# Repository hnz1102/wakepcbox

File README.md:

<div align="center">
  <h1><code>Wake PC Box</code></h1>
  
</div>

# Wake PC Box - Wake On LAN Packet Transmitting Box

Video

This is the small control box that can wake up the PC using Wake On LAN. You can just push a button, PCs will wake up from the power off status.
There is no need to start up another PC in order to start up a PC with Wake On Lan. Wake on LAN packets are sent via WiFi LAN.
The Box has a battery, and you can charge it from a USB Type-C port. Once charging full, you can use it for a month. If any buttons are not pressed for the specified time (default 30 seconds), the box will sleep automatically and conserve battery power. Up to four PCs can be registered.

# Update History
- 2024-05-30 : Initial Release
- 2026-02-14 : Update code for ESP-IDF V5.4.2 and update README.md
- 2026-06-20 : v0.2.0 - Add WPS PBC mode support, fix WPS display overlap, fix WiFi menu not reflecting WPS credentials immediately

# How it works

This box can send a Wake on LAN packet to the Wireless Access Point. To transfer the packet, the Access Point needs to be set to `Bridge Mode`. If `Router Mode` is set, the Access Point won't transfer to the wired LAN. 

# Feature

**Quick Wake Up** -  Simply press one of the up, down, left, or right buttons to turn on the PC corresponding to that button. 4 PCs can be registered.

**Microcontroller on board** - No need for a PC when you turn on another PC. Directly send packets to the target PCs. 

**Transmit a packet via WiFi** - Wake-on LAN packets are transmitted via Wireless Network.

**Battery Powered** - Using LiPo battery. It can run for a month (In this case, every day a few times used).

**Small Handy Box** - This box is only 60mm(W) x 23mm(H) x 80mm(D) size. No need for any cables, it works. 

**Configurable** - Setting parameters are set from the display menu. SSID/Password/Target PC Hardware Address(4 PCs)/Time Zone/Sleep Time/Sleep Mode/Display Off Time/Reset Settings.

**WPS Support** - If `wps_enable = "true"` and `wifi_ssid` is empty in `cfg.toml`, the device enters WPS PBC (Push Button Configuration) mode on first boot. Press the WPS button on your router within 120 seconds. The obtained SSID and password are saved to NVS automatically, and subsequent boots connect normally without WPS.

# How to Use the Box
At first, you can set the WiFi SSID and PSK-Password in one of two ways:

**Option A: Manual entry via menu** - Push the Center Key to open the setting menu, select `WiFi`, then enter your SSID and password using the direction keys.

**Option B: WPS PBC mode** - Set `wps_enable = "true"` and leave `wifi_ssid` empty in `cfg.toml` before flashing. On first boot, the device displays "WPS MODE" and waits up to 120 seconds. Press the WPS button on your router to transfer the credentials automatically. The SSID and password are saved and WPS mode is disabled for subsequent boots.
Next, set the Hardware Address(Ethernet MAC Address) of the PC that you want to wake up. Select `HW Address` and push Center Key, select from `PC1` to `PC4`, push Center key, then enter your Hardware Address like `00:11:22:33:44:55`. 

After setting, just push button corresponding the target.(Up Key : PC1, Down Key : PC2, Left Key: PC3, Right Key: PC4)

To charge a battery, just connect to a USB Type-C port from the bus-powered USB port. During the charge, the CHG LED is RED ON. After the charging is full, the FUL LED is GREEN ON. And the charging will be stopped automatically.

Assembled PCB

Set in Box

# How to build from code and Install to the unit.

Using Ubuntu 22.04.3 LTS and ESP-IDF V5.4.2

1. Install Rust Compiler
```bash
sudo apt update && sudo apt -y install git python3 python3-pip gcc build-essential curl pkg-config libudev-dev libtinfo5 clang libclang-dev llvm-dev udev libssl-dev python3.10-venv
curl --proto '=https' --tlsv1.2 -sSf https://sh.rustup.rs | sh
```
You can see the install menu, select No.1. After installation, set the environment variable.

```bash
. "$HOME/.cargo/env"
```

2. Install toolchain for ESP32-C3
```bash
cargo install ldproxy
cargo install espup
cargo install cargo-espflash
```

3. Install ESP-IDF and set the environment variable.
```bash
espup install
espup update
```

Then, run the following command to set the environment for the ESP32-C3 toolchain:
```bash
. ./export-esp.sh
```

4. Add UDEV rules
```bash
sudo sh -c 'echo "SUBSYSTEMS==\"usb\", ATTRS{idVendor}==\"303a\", ATTRS{idProduct}==\"1001\", MODE=\"0666\"" > /etc/udev/rules.d/99-esp32.rules'
sudo udevadm control --reload-rules
sudo udevadm trigger
```

5. Download Current-Logger code
```bash
git clone https://github.com/hnz1102/wakepcbox.git
cd wakepcbox
``` 
6. Setting WiFi SSID, Password, and InfluxDB server IP address.
```bash
cfg.toml

[wakepcbox]
wifi_ssid = "<SSID>"      # Set your AP SSID. Leave empty to use WPS mode.
wifi_psk = "<Password>"   # Set password for SSID.
wps_enable = "false"       # Set "true" to use WPS PBC mode on first boot (requires wifi_ssid to be empty).
target_mac_address1 = "00:00:00:00:00:00"  # Set Hardware Address(MAC Address) for wakeup.
target_mac_address2 = "00:00:00:00:00:00"
target_mac_address3 = "00:00:00:00:00:00"
target_mac_address4 = "00:00:00:00:00:00"
timezone_offset = "0"
idle_in_sleep_time = "30"
sleep_mode = "light"
display_off_time = "30"
wakeup_interval = "10"
```
7. Build code and writing flash
```bashbash
cargo build --release
```

8. Connecting the board and Set device and set toolchain.

Connecting the Box by USB Type-C to this code building PC. Then, 

```bash
cargo espflash board-info

✔ Use serial port '/dev/ttyACM0' - USB JTAG/serial debug unit? · yes
✔ Remember this serial port for future use? · yes
[2026-02-14T04:41:35Z INFO ] Serial port: '/dev/ttyACM0'
[2026-02-14T04:41:35Z INFO ] Connecting...
[2026-02-14T04:41:36Z INFO ] Using flash stub
Chip type:         esp32c3 (revision v0.4)
Crystal frequency: 40 MHz
Flash size:        4MB
Features:          WiFi, BLE
MAC address:       a0:76:4e:b3:64:c0

Security Information:
=====================
Flags: 0x00000000 (0)
Key Purposes: [0, 0, 0, 0, 0, 0, 12]
Chip ID: 5
API Version: 3
Secure Boot: Disabled
Flash Encryption: Disabled
SPI Boot Crypt Count (SPI_BOOT_CRYPT_CNT): 0x0
```

9. Writing flash
```bash
cargo espflash flash --release --monitor

[2026-02-14T04:43:53Z INFO ] Serial port: '/dev/ttyACM0'
[2026-02-14T04:43:53Z INFO ] Connecting...
[2026-02-14T04:43:53Z INFO ] Using flash stub
   Compiling wakepcbox v0.1.0 (/wakepcbox)
    Finished `release` profile [optimized] target(s) in 4.22s
Chip type:         esp32c3 (revision v0.4)
Crystal frequency: 40 MHz
Flash size:        4MB
Features:          WiFi, BLE
MAC address:       a0:76:4e:b3:64:c0
App/part. size:    1,644,080/3,145,728 bytes, 52.26%
[00:00:00] [========================================]      13/13      0x0      Verifying... OK!                                                                                                                                                       [00:00:00] [========================================]       1/1       0x8000   Skipped! (checksum matches)                                                                                                                                            
[00:00:15] [========================================]     887/887     0x10000  Verifying... OK!                                                                                                                                                       [2026-02-14T04:44:16Z INFO ] Flashing has completed!

And automatically boot!
```
## Schematic, PCB Gabar and Container 3D Data

There is a Schematic data in the hardware directory including 3D printing data. 

## LICENSE
This source code is licensed under MIT. Other Hardware Schematic documents are licensed under CC-BY-SA V4.0.

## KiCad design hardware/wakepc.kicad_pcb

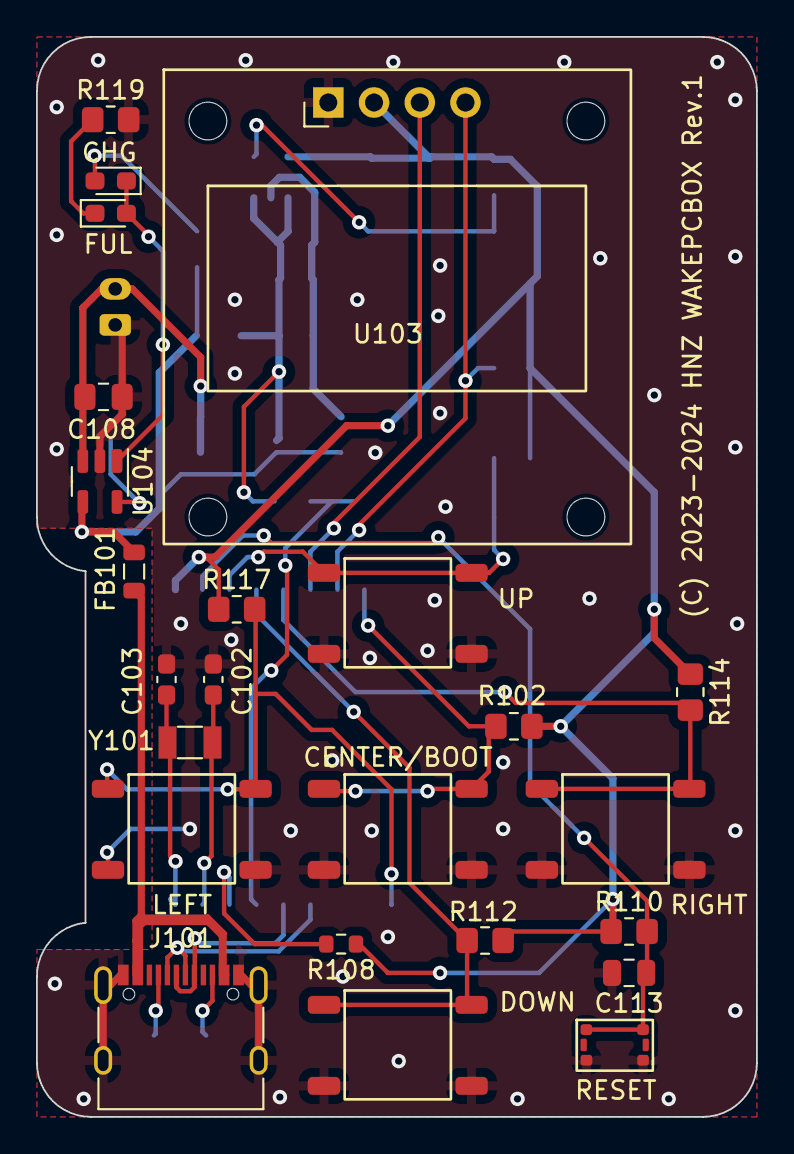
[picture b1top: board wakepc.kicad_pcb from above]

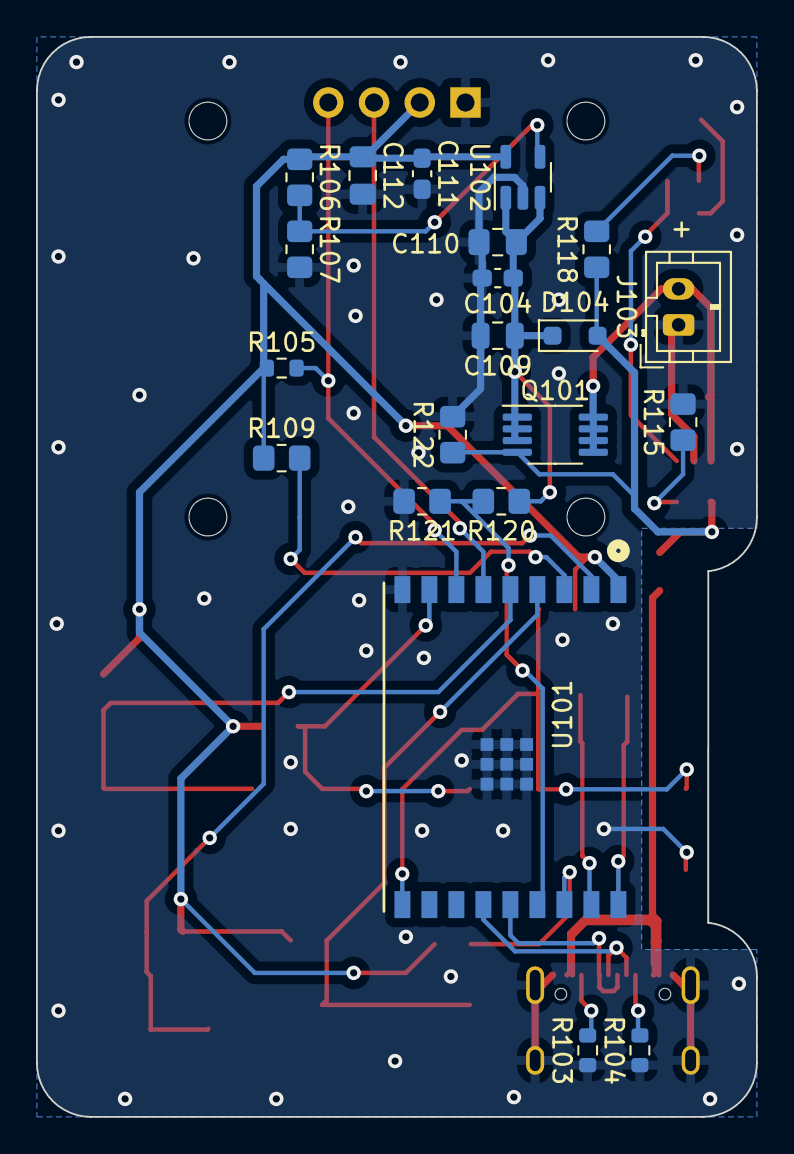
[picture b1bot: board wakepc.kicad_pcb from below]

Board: 2 copper layers, 40.0 x 60.0 mm, 45 parts (21 on the bottom side), 27 nets.

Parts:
C102, C103: 16pF; C_0603_1608Metric_Pad1.08x0.95mm_HandSolder
C104, C111: 0.1uF; C_0603_1608Metric_Pad1.08x0.95mm_HandSolder
C108: 4.7uF; C_0805_2012Metric_Pad1.18x1.45mm_HandSolder
C109, C113: 1uF; C_0805_2012Metric
C110, C112: 10uF; C_0805_2012Metric_Pad1.18x1.45mm_HandSolder
D102: LED RED; LED_0603_1608Metric_Pad1.05x0.95mm_HandSolder
D103: LED GREEN; LED_0603_1608Metric_Pad1.05x0.95mm_HandSolder
D104: NSR0340HT1G; D_SOD-323_HandSoldering
FB101: MH2029-601Y; L_0805_2012Metric
J101: USB4105-GF-A; USB_C_5077CR-16-SMC2-BK-TR
J103: LiPo BATTERY; JST_PH_B2B-PH-K_1x02_P2.00mm_Vertical
Q101: IRF7606TRPBF; MSOP-8_3x3mm_P0.65mm
R102, R109, R110, R112, R114, R117: 10K; R_0805_2012Metric_Pad1.20x1.40mm_HandSolder
R103, R104: 5.1K; R_0603_1608Metric
R105, R108: 10K; R_0603_1608Metric
R106, R120, R121: 20K 1%; R_0805_2012Metric_Pad1.20x1.40mm_HandSolder
R107: 12K 1%; R_0805_2012Metric_Pad1.20x1.40mm_HandSolder
R115: 2K; R_0805_2012Metric_Pad1.20x1.40mm_HandSolder
R118, R119: 330; R_0805_2012Metric_Pad1.20x1.40mm_HandSolder
R122: 100K; R_0805_2012Metric_Pad1.20x1.40mm_HandSolder
SW101, SW103, SW104, SW105, SW106: TS-06104
SW102: 3.5x2.6 Tact SW; WS-TASV SMT Tact Switch
U101: ESP32-C3-WROOM-02-N4; IC18_ESP32-C3-WROOM-02-N4_EXP
U102: SPX3819M5-L; SOT-23-5
U103: SSD1306_DISPLAY; OLED I2C DISPLAY
U104: MCP73831-2-OT; SOT-23-5
Y101: 32.7680KHz; Crystal_SMD_3215-2Pin_3.2x1.5mm

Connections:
+3.3V: C111.1, C112.1, R102.1, R105.1, R106.1, R108.1, R109.1, R110.1, R112.1, R114.1, R117.1, U101.1 (3V3), U102.5 (OUT), U103.2 (VCC)
/GPIO0: C103.1, U101.18 (IO0), Y101.2
/GPIO1: C102.1, U101.17 (IO1), Y101.1
/GPIO2: R108.2, U101.16 (IO2)
/GPIO3: R120.2, R121.1, U101.15 (IO3)
/GPIO4/TMS: R109.2, SW104.C, SW104.D, U101.3 (IO4)
/GPIO5/TDI: R112.2, SW103.C, SW103.D, U101.4 (IO5)
/GPIO6/TCK: R114.2, SW105.C, SW105.D, U101.5 (IO6)
/GPIO7/TDO: U101.6 (IO7), U103.3 (SCL)
/GPIO8: R105.2, U101.7 (IO8), U103.4 (SDA)
/GPIO9: R102.2, SW101.C, SW101.D, U101.8 (IO9)
/GPIO10: R117.2, SW106.C, SW106.D, U101.10 (IO10)
/USBDM: J101.A7 (D-), J101.B7 (D-), U101.13 (IO18)
/USBDP: J101.A6 (D+), J101.B6 (D+), U101.14 (IO19)
/USBVDD: D104.2 (A), FB101.2, Q101.4 (G), R118.1, R122.1, U104.4 (V_{DD})
/VBAT: C108.1, J103.2, Q101.5 (D), Q101.6 (D), Q101.7 (D), Q101.8 (D), U104.3 (V_{BAT})
/VOUT: C104.1, C109.1, C110.1, D104.1 (K), Q101.1 (S), Q101.2 (S), Q101.3 (S), R120.1, U102.1 (IN), U102.3 (EN)
/~RESET: C113.1, R110.2, SW102.1, SW102.2, U101.2 (EN)
GND: C102.2, C103.2, C104.2, C108.2, C109.2, C110.2, C111.2, C112.2, C113.2, J101.A1 (GND), J101.A12 (GND), J101.B1 (GND), J101.B12 (GND), J101.S1 (SHIELD), J103.1, R103.1, R104.1, R107.2, R115.2, R119.2, R121.2, R122.2, SW101.A, SW101.B, SW102.3 (K), SW102.4 (A), SW103.A, SW103.B, SW104.A, SW104.B, SW105.A, SW105.B, SW106.A, SW106.B, U101.9 (GND), U101.19 (GND), U101.20 (GND), U101.21 (GND), U101.22 (GND), U101.23 (GND), U101.24 (GND), U101.25 (GND), U101.26 (GND), U101.27 (GND), U102.2 (GND), U103.1 (GND), U104.2 (V_{SS})
unnamed: D102.2 (A), R118.2
unnamed: D102.1 (K), D103.2 (A), U104.1 (STAT)
unnamed: D103.1 (K), R119.1
unnamed: FB101.1, J101.A4 (VBUS), J101.A9 (VBUS), J101.B4 (VBUS), J101.B9 (VBUS)
unnamed: J101.A5 (CC1), R104.2
unnamed: J101.B5 (CC2), R103.2
unnamed: R106.2, R107.1, U102.4 (ADJ)
unnamed: R115.1, U104.5 (PROG)

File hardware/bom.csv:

Reference,Value,Footprint,Datasheet,digikey,distributor,Qty
"C102, C103",16pF,Capacitor_SMD:C_0603_1608Metric_Pad1.08x0.95mm_HandSolder,~,,,2
"C104, C111",0.1uF,Capacitor_SMD:C_0603_1608Metric_Pad1.08x0.95mm_HandSolder,~,,https://www.digikey.com/en/products/detail/yageo/CC0603ZRY5V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,2
C108,4.7uF,Capacitor_SMD:C_0805_2012Metric_Pad1.18x1.45mm_HandSolder,~,,https://www.digikey.com/en/products/detail/yageo/CC0805ZRY5V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,1
"C109, C113",1uF,Capacitor_SMD:C_0805_2012Metric,~,,https://www.digikey.com/en/products/detail/yageo/CC0805ZRY5V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,2
"C110, C112",10uF,Capacitor_SMD:C_0805_2012Metric_Pad1.18x1.45mm_HandSolder,~,,https://www.digikey.com/en/products/detail/murata-electronic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,2
D102,LED RED,LED_SMD:LED_0603_1608Metric_Pad1.05x0.95mm_HandSolder,~,,https://www.digikey.com/en/products/detail/harvatek-corporat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,1
D103,LED GREEN,LED_SMD:LED_0603_1608Metric_Pad1.05x0.95mm_HandSolder,~,,https://www.digikey.com/en/products/detail/harvatek-corporat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,1
D104,NSR0340HT1G,Diode_SMD:D_SOD-323_HandSoldering,https://www.onsemi.com/pub/Collateral/NSR0340H-D.PDF,,https://www.digikey.com/en/products/detail/onsemi/NSR0340HT1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,1
FB101,MH2029-601Y,Inductor_SMD:L_0805_2012Metric,~,,https://www.digikey.com/en/products/detail/bourns-inc/MH2029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,1
J101,USB4105-GF-A,Library:USB_C_5077CR-16-SMC2-BK-TR,https://www.usb.org/sites/default/files/documents/usb_type-c.zip,,https://www.digikey.com/en/products/detail/gct/USB4105-GF-A/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,1
J103,LiPo BATTERY,Connector_JST:JST_PH_B2B-PH-K_1x02_P2.00mm_Vertical,~,,https://www.digikey.com/en/products/detail/jst-sales-america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,1
Q101,IRF7606TRPBF,Package_SO:MSOP-8_3x3mm_P0.65mm,http://www.irf.com/product-info/datasheets/data/irf7606pbf.pdf,,https://www.digikey.com/en/products/detail/infineon-technolo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,1
"R102, R109, R110, R112, R114, R117",10K,Resistor_SMD:R_0805_2012Metric_Pad1.20x1.40mm_HandSolder,~,,https://www.digikey.jp/en/products/detail/yageo/RC0603JR-101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,6
"R103, R104",5.1K,Resistor_SMD:R_0603_1608Metric,~,,https://www.digikey.com/en/products/detail/yageo/RC0603JR-07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,2
"R105, R108",10K,Resistor_SMD:R_0603_1608Metric,~,,https://www.digikey.jp/en/products/detail/yageo/RC0603JR-101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,2
"R106, R120, R121",20K 1%,Resistor_SMD:R_0805_2012Metric_Pad1.20x1.40mm_HandSolder,~,,https://www.digikey.jp/en/products/detail/yageo/RC0603FR-072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,3
R107,12K 1%,Resistor_SMD:R_0805_2012Metric_Pad1.20x1.40mm_HandSolder,~,,https://www.digikey.com/en/products/detail/yageo/RC0603FR-07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,1
R115,2K,Resistor_SMD:R_0805_2012Metric_Pad1.20x1.40mm_HandSolder,~,,https://www.digikey.com/en/products/detail/yageo/RC0603JR-07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,1
"R118, R119",330,Resistor_SMD:R_0805_2012Metric_Pad1.20x1.40mm_HandSolder,~,,https://www.digikey.com/en/products/detail/yageo/RC0603JR-13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,2
R122,100K,Resistor_SMD:R_0805_2012Metric_Pad1.20x1.40mm_HandSolder,~,,https://www.digikey.com/en/products/detail/yageo/RC0603JR-07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,1
"SW101, SW103-SW106",TS-06104,Library:TS-06104,,,https://akizukidenshi.com/catalog/g/g115969/,5
SW102,3.5x2.6 Tact SW,Library:WS-TASV SMT Tact Switch,,,https://www.digikey.com/en/products/detail/w%C3%BCrth-elektr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,1
U101,ESP32-C3-WROOM-02-N4,Library:IC18_ESP32-C3-WROOM-02-N4_EXP,ESP32-C3-WROOM-02-N4,,https://www.digikey.com/en/products/detail/espressif-systems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,1
U102,SPX3819M5-L,Package_TO_SOT_SMD:SOT-23-5,https://www.exar.com/content/document.ashx?id=22106&language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,,https://www.digikey.com/en/products/detail/maxlinear-inc/SPX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,1
U103,SSD1306_DISPLAY,Library:OLED I2C DISPLAY,,,https://akizukidenshi.com/catalog/g/g112031/,1
U104,MCP73831-2-OT,Package_TO_SOT_SMD:SOT-23-5,http://ww1.microchip.com/downloads/en/DeviceDoc/20001984g.pdf,,https://www.digikey.com/en/products/detail/microchip-technol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,1
Y101,32.7680KHz,Crystal:Crystal_SMD_3215-2Pin_3.2x1.5mm,~,2151-RT3215-32.768-12.5-TRCT-ND,https://www.digikey.com/en/products/detail/raltron-electroni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,1

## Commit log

2024-01-29 Add hardware data
2024-02-02 Fixed typo
2024-05-30 Fixed install packages in the README
2026-06-20 v0.2.0: Add WPS PBC support, fix display overlap and menu update
    - Add WPS PBC (Push Button Configuration) mode
    - Enabled via wps_enable=true in cfg.toml with empty wifi_ssid
    - Waits up to 120s for router WPS button press
    - Saves obtained SSID/PSK to NVS; disables WPS for subsequent boots
    - Fix WPS waiting display overlap
    - Remove \n from set_status messages in wifi.rs

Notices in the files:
hardware/wakepc.kicad_pcb:
(C) 2023-2024 HNZ WAKEPCBOX Rev.1
